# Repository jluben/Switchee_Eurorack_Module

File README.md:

# Switchee Eurorack Module
Switchee is a Eurorack signal switcher using the ATSAMD10D14A. It's a fairly simple design that uses the MCU to control DG447 analog signal switchers. The DG447 a cheap and can handle the full voltage bandwidth of typical Eurorack signals. Assemble is with SMD components, and the PCB falls into budget range of JLCPCB. When this was designed in 2022, you could build a unit for under $30. Even cheaper if you wanted to build ten units.

The default behavior is to advance the output from one to four for each trigger input. The mode button changes this behavior. There are three counting modes: linear, exponential (up to 1024), and fibonacci. In exponential mode, it takes an increase number of triggers to advance the counter and change the output. For example, 2, 4, 8, 16, etc. The fibonacci mode is similiar: it takes 1, 1, 2, 3, 5, 8 and so on triggers to change the output routing.

The module has:
* A TRIGGER input that changes the output
* A Signal input that is buffered and routed to one of four outputs
* A Reset input that changes the switching back to Output One
* A Mode button 

This project includes the PCB, PCB front panel, and firmware. Firmware is downloaded to the ATSAMD10 via ATMEL ICE.

The PCB is done in Kicad. There are fab-ready gerbers in the gerbers/ directory. The main firmware file is in firmware/main.c

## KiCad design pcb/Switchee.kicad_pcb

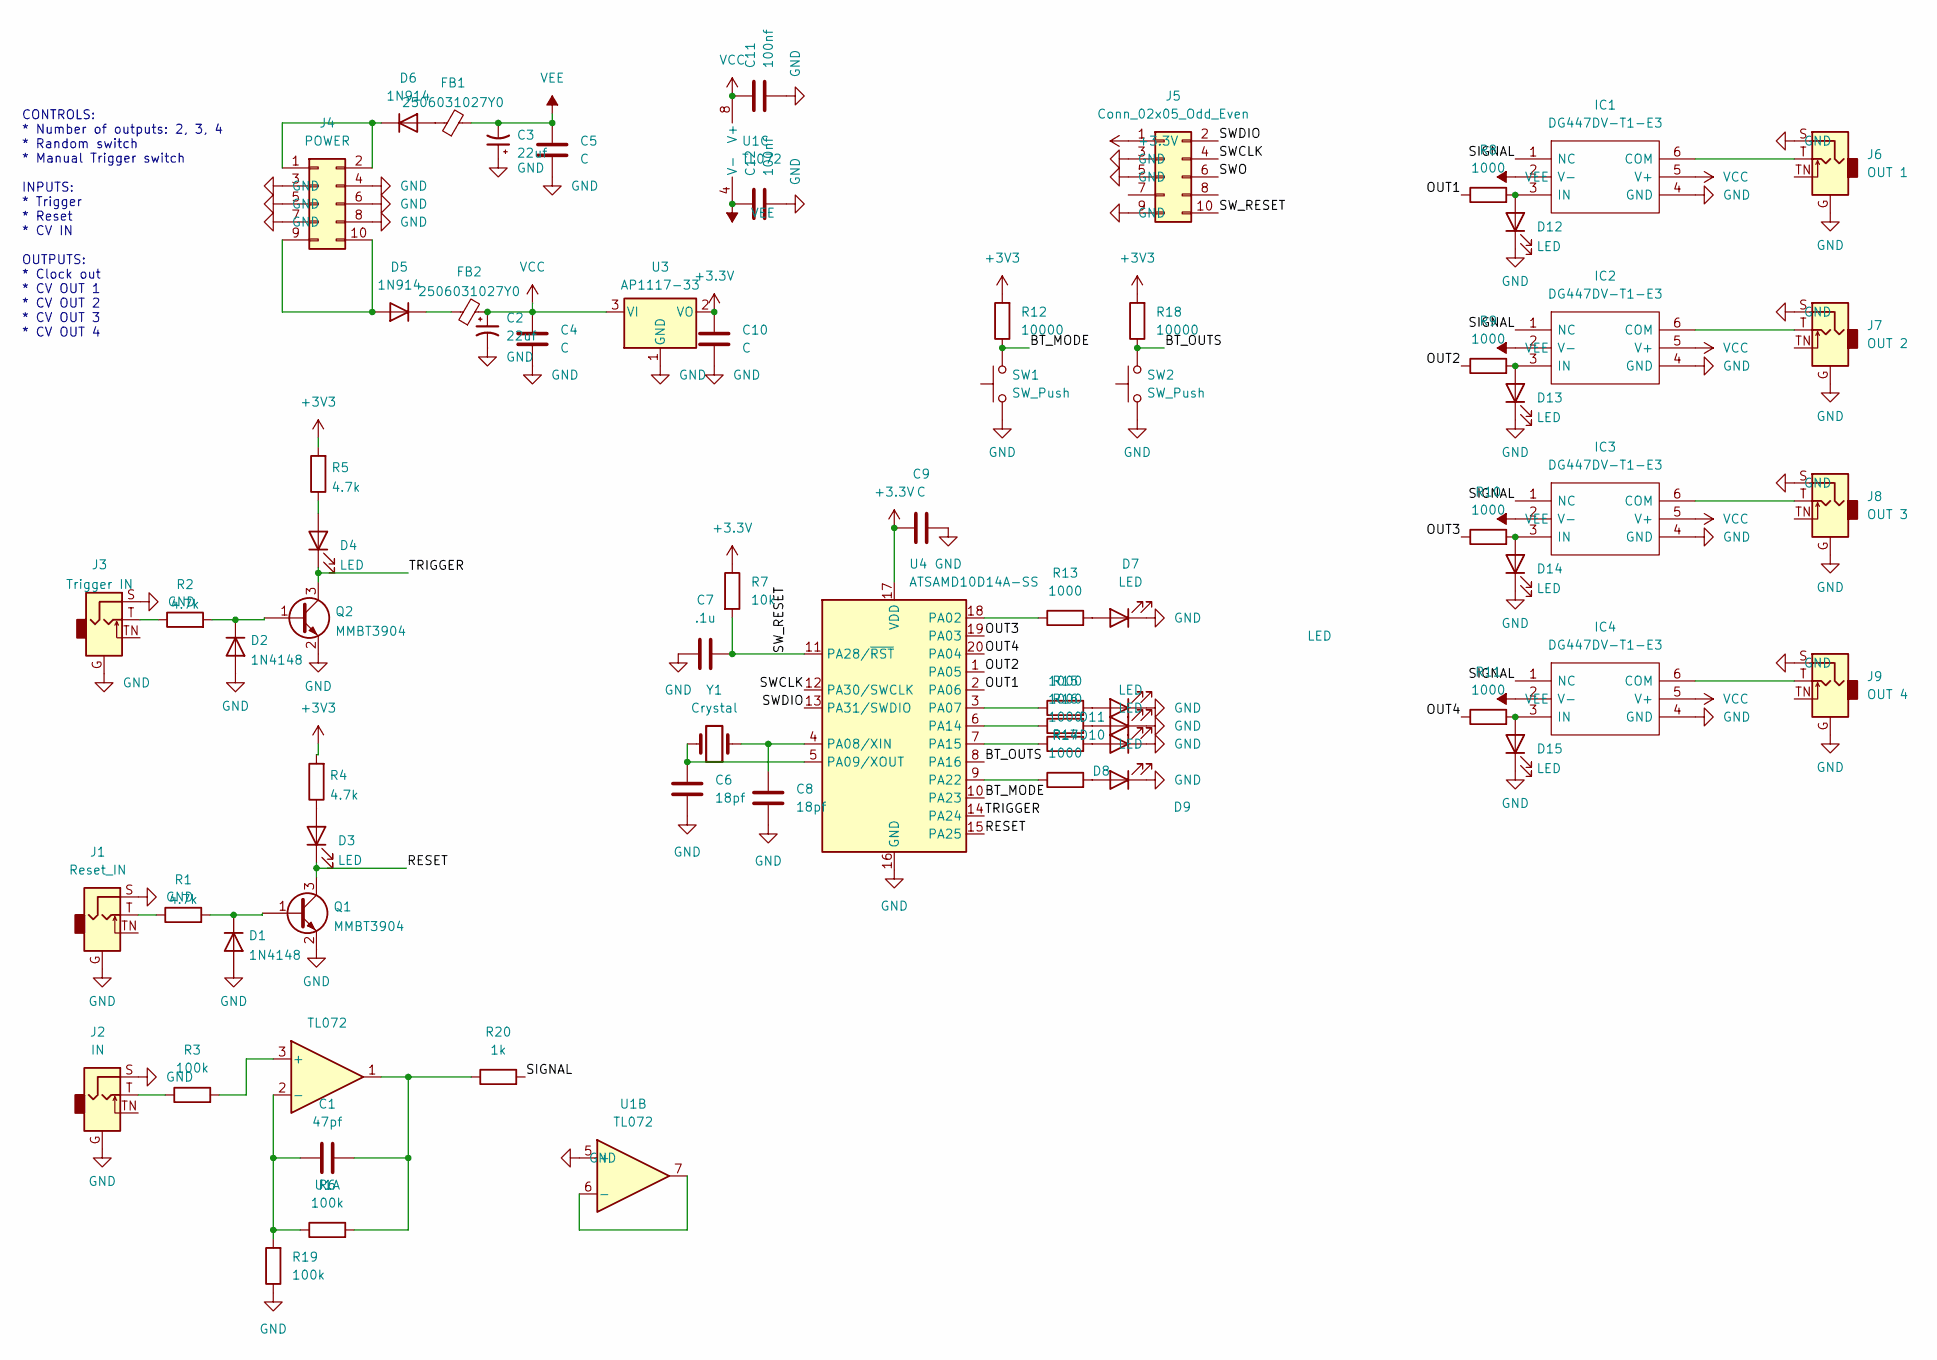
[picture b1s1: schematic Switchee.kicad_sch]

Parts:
C1: 47pf; C_0805_2012Metric_Pad1.18x1.45mm_HandSolder
C2, C3: 22uf; C_1206_3216Metric_Pad1.33x1.80mm_HandSolder
C4, C5, C9, C10: C; C_0805_2012Metric_Pad1.18x1.45mm_HandSolder
C6, C8: 18pf; C_0805_2012Metric_Pad1.18x1.45mm_HandSolder
C7: .1u; C_0805_2012Metric_Pad1.18x1.45mm_HandSolder
C11, C12: 100nf; C_0805_2012Metric_Pad1.18x1.45mm_HandSolder
D1, D2: 1N4148; D_SOD-123
D3, D4, D7, D8, D9, D10, D11, D12, D13, D14, D15: LED; LED_D3.0mm
D5, D6: 1N914; D_SOD-123
FB1, FB2: 2506031027Y0; R_0805_2012Metric_Pad1.20x1.40mm_HandSolder
IC1, IC2, IC3, IC4: DG447DV-T1-E3; SOP95P284X110-6N; Mouser Part Number 781-DG447DV-E3
J1: Reset_IN; Jack_3.5mm_QingPu_WQP-PJ398SM_Vertical_CircularHoles
J2: IN; Jack_3.5mm_QingPu_WQP-PJ398SM_Vertical_CircularHoles
J3: Trigger IN; Jack_3.5mm_QingPu_WQP-PJ398SM_Vertical_CircularHoles
J4: POWER; PinHeader_2x05_P2.54mm_Vertical
J5: Conn_02x05_Odd_Even; PinHeader_2x05_P1.27mm_Vertical
J6: OUT 1; Jack_3.5mm_QingPu_WQP-PJ398SM_Vertical_CircularHoles
J7: OUT 2; Jack_3.5mm_QingPu_WQP-PJ398SM_Vertical_CircularHoles
J8: OUT 3; Jack_3.5mm_QingPu_WQP-PJ398SM_Vertical_CircularHoles
J9: OUT 4; Jack_3.5mm_QingPu_WQP-PJ398SM_Vertical_CircularHoles
Q1, Q2: MMBT3904; SOT-23
R1, R2, R4, R5: 4.7k; R_0805_2012Metric_Pad1.20x1.40mm_HandSolder
R3, R6, R19: 100k; R_0805_2012Metric_Pad1.20x1.40mm_HandSolder
R7: 10k; R_0805_2012Metric_Pad1.20x1.40mm_HandSolder
R8, R9, R10, R11, R13, R14, R15, R16, R17: 1000; R_0805_2012Metric_Pad1.20x1.40mm_HandSolder
R12, R18: 10000; R_0805_2012Metric_Pad1.20x1.40mm_HandSolder
R20: 1k; R_0805_2012Metric_Pad1.20x1.40mm_HandSolder
SW1, SW2: SW_Push; SW_PUSH_6mm
U1: TL072; SOIC-8_3.9x4.9mm_P1.27mm
U3: AP1117-33; SOT-223-3_TabPin2
U4: ATSAMD10D14A-SS; SOIC-20W_7.5x12.8mm_P1.27mm
Y1: Crystal; Crystal_Round_D1.0mm_Vertical

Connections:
/BT_MODE: R12.1, SW1.2, U4.10 (PA23)
/BT_OUTS: R18.1, SW2.2, U4.8 (PA16)
/OUT1: R8.1, U4.2 (PA06)
/OUT2: R9.1, U4.1 (PA05)
/OUT3: R10.1, U4.19 (PA03)
/OUT4: R11.1, U4.20 (PA04)
/RESET: D3.1 (K), Q1.3 (C), U4.15 (PA25)
/SIGNAL: IC1.1 (NC), IC2.1 (NC), IC3.1 (NC), IC4.1 (NC), R20.2
/SWCLK: J5.4, U4.12 (PA30/SWCLK)
/SWDIO: J5.2, U4.13 (PA31/SWDIO)
/SWO: J5.6
/SW_RESET: C7.1, J5.10, R7.2, U4.11 (PA28/~RST)
/TRIGGER: D4.1 (K), Q2.3 (C), U4.14 (PA24)
GND: C2.2, C3.1, C4.2, C5.2, C6.2, C7.2, C8.2, C9.2, C10.2, C11.2, C12.2, D1.2 (A), D2.2 (A), D7.1 (K), D8.1 (K), D9.1 (K), D10.1 (K), D11.1 (K), D12.1 (K), D13.1 (K), D14.1 (K), D15.1 (K), IC1.4 (GND), IC2.4 (GND), IC3.4 (GND), IC4.4 (GND), J1.G, J1.S, J2.G, J2.S, J3.G, J3.S, J4.3, J4.4, J4.5, J4.6, J4.7, J4.8, J5.3, J5.5, J5.9, J6.G, J6.S, J7.G, J7.S, J8.G, J8.S, J9.G, J9.S, Q1.2 (E), Q2.2 (E), R19.1, SW1.1, SW2.1, U1.5 (+), U3.1 (GND), U4.16 (GND)
unnamed: C1.2, R6.2, R20.1, U1.1
unnamed: C6.1, U4.5 (PA09/XOUT), Y1.2
unnamed: C8.1, U4.4 (PA08/XIN), Y1.1
unnamed: D1.1 (K), Q1.1 (B), R1.2
unnamed: D2.1 (K), Q2.1 (B), R2.2
unnamed: D3.2 (A), R4.1
unnamed: D4.2 (A), R5.1
unnamed: D5.1 (K), FB2.1
unnamed: D5.2 (A), J4.9, J4.10
unnamed: D6.1 (K), J4.1, J4.2
unnamed: D6.2 (A), FB1.1
unnamed: D7.2 (A), R13.2
unnamed: D8.2 (A), R14.2
unnamed: D9.2 (A), R15.2
unnamed: D10.2 (A), R16.2
unnamed: D11.2 (A), R17.2
unnamed: D12.2 (A), IC1.3 (IN), R8.2
unnamed: D13.2 (A), IC2.3 (IN), R9.2
unnamed: D14.2 (A), IC3.3 (IN), R10.2
unnamed: D15.2 (A), IC4.3 (IN), R11.2
unnamed: IC1.6 (COM), J6.T
unnamed: IC2.6 (COM), J7.T
unnamed: IC3.6 (COM), J8.T
unnamed: IC4.6 (COM), J9.T
unnamed: J1.T, R1.1
unnamed: J2.T, R3.1
unnamed: J3.T, R2.1
unnamed: R3.2, U1.3 (+)
unnamed: R13.1, U4.18 (PA02)
unnamed: R14.1, U4.9 (PA22)
unnamed: R15.1, U4.6 (PA14)
unnamed: R16.1, U4.7 (PA15)
unnamed: R17.1, U4.3 (PA07)
unnamed: C1.1, R6.1, R19.2, U1.2 (-)
unnamed: U1.6 (-), U1.7
VCC: C2.1, C4.1, C11.1, FB2.2, IC1.5 (V+), IC2.5 (V+), IC3.5 (V+), IC4.5 (V+), U1.8 (V+), U3.3 (VI)
VEE: C3.2, C5.1, C12.1, FB1.2, IC1.2 (V-), IC2.2 (V-), IC3.2 (V-), IC4.2 (V-), U1.4 (V-)

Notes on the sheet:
CONTROLS: * Number of outputs: 2, 3, 4 * Random switch * Manual Trigger switch INPUTS: * Trigger * Reset * CV IN OUTPUTS: * Clock out * CV OUT 1 * CV OUT 2 * CV OUT 3 * CV OUT 4

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
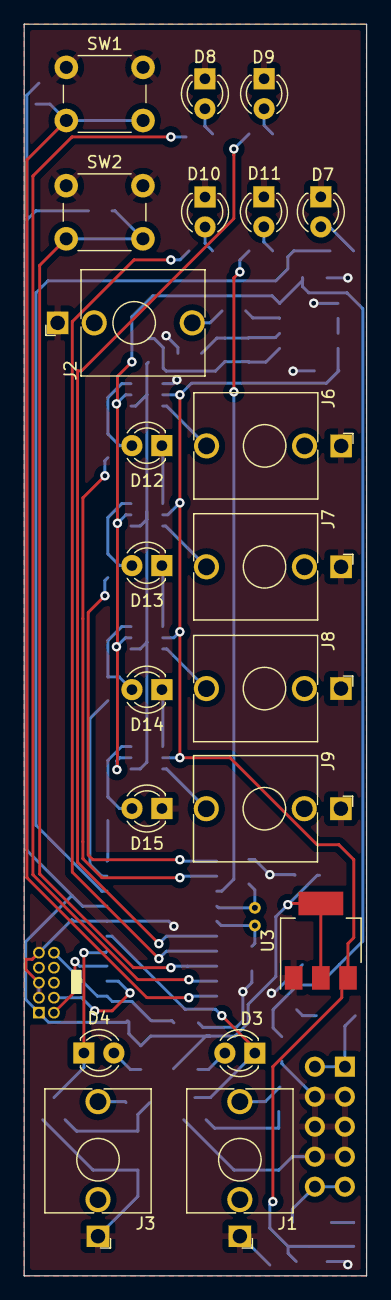
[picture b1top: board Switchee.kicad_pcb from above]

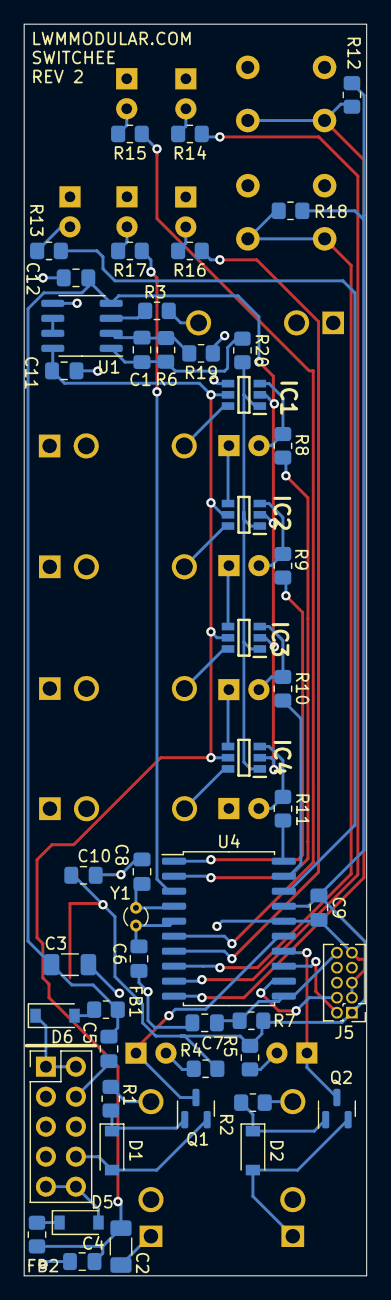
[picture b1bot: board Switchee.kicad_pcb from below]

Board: 2 copper layers, 29.0 x 106.0 mm, 70 parts (49 on the bottom side), 51 nets.

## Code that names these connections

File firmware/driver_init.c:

/*
 * Code generated from Atmel Start.
 *
 * This file will be overwritten when reconfiguring your Atmel Start project.
 * Please copy examples or other code you want to keep to a separate file
 * to avoid losing it when reconfiguring.
 */

#include "driver_init.h"
#include <peripheral_clk_config.h>
#include <utils.h>
#include <hal_init.h>
#include <hpl_gclk_base.h>
#include <hpl_pm_base.h>

#include <hpl_rtc_base.h>

struct timer_descriptor TIMER_0;

struct flash_descriptor FLASH_0;

struct dac_sync_descriptor DAC_0;

void FLASH_0_CLOCK_init(void)
{

	_pm_enable_bus_clock(PM_BUS_APBB, NVMCTRL);
}

void FLASH_0_init(void)
{
	FLASH_0_CLOCK_init();
	flash_init(&FLASH_0, NVMCTRL);
}

void delay_driver_init(void)
{
	delay_init(SysTick);
}

/**
 * \brief Timer initialization function
 *
 * Enables Timer peripheral, clocks and initializes Timer driver
 */
static void TIMER_0_init(void)
{
	_pm_enable_bus_clock(PM_BUS_APBA, RTC);
	_gclk_enable_channel(RTC_GCLK_ID, CONF_GCLK_RTC_SRC);
	timer_init(&TIMER_0, RTC, _rtc_get_timer());
}

void DAC_0_PORT_init(void)
{
}

void DAC_0_CLOCK_init(void)
{

	_pm_enable_bus_clock(PM_BUS_APBC, DAC);
	_gclk_enable_channel(DAC_GCLK_ID, CONF_GCLK_DAC_SRC);
}

void DAC_0_init(void)
{
	DAC_0_CLOCK_init();
	dac_sync_init(&DAC_0, DAC);
	DAC_0_PORT_init();
}

void system_init(void)
{
	init_mcu();

	// GPIO on PA02

	// Disable digital pin circuitry
	gpio_set_pin_direction(LED7, GPIO_DIRECTION_OFF);

	gpio_set_pin_function(LED7, GPIO_PIN_FUNCTION_OFF);

	// GPIO on PA03

	gpio_set_pin_level(OUT3,
	                   // <y> Initial level
	                   // <id> pad_initial_level
	                   // <false"> Low
	                   // <true"> High
	                   false);

	// Set pin direction to output
	gpio_set_pin_direction(OUT3, GPIO_DIRECTION_OUT);

	gpio_set_pin_function(OUT3, GPIO_PIN_FUNCTION_OFF);

	// GPIO on PA04

	gpio_set_pin_level(OUT4,
	                   // <y> Initial level
	                   // <id> pad_initial_level
	                   // <false"> Low
	                   // <true"> High
	                   false);

	// Set pin direction to output
	gpio_set_pin_direction(OUT4, GPIO_DIRECTION_OUT);

	gpio_set_pin_function(OUT4, GPIO_PIN_FUNCTION_OFF);

	// GPIO on PA05

	gpio_set_pin_level(OUT2,
	                   // <y> Initial level
	                   // <id> pad_initial_level
	                   // <false"> Low
	                   // <true"> High
	                   false);

	// Set pin direction to output
	gpio_set_pin_direction(OUT2, GPIO_DIRECTION_OUT);

	gpio_set_pin_function(OUT2, GPIO_PIN_FUNCTION_OFF);

	// GPIO on PA06

	gpio_set_pin_level(OUT1,
	                   // <y> Initial level
	                   // <id> pad_initial_level
	                   // <false"> Low
	                   // <true"> High
	                   false);

	// Set pin direction to output
	gpio_set_pin_direction(OUT1, GPIO_DIRECTION_OUT);

	gpio_set_pin_function(OUT1, GPIO_PIN_FUNCTION_OFF);

	// GPIO on PA07

	gpio_set_pin_level(LED11,
	                   // <y> Initial level
	                   // <id> pad_initial_level
	                   // <false"> Low
	                   // <true"> High
	                   false);

	// Set pin direction to output
	gpio_set_pin_direction(LED11, GPIO_DIRECTION_OUT);

	gpio_set_pin_function(LED11, GPIO_PIN_FUNCTION_OFF);

	// GPIO on PA14

	gpio_set_pin_level(LED9,
	                   // <y> Initial level
	                   // <id> pad_initial_level
	                   // <false"> Low
	                   // <true"> High
	                   false);

	// Set pin direction to output
	gpio_set_pin_direction(LED9, GPIO_DIRECTION_OUT);

	gpio_set_pin_function(LED9, GPIO_PIN_FUNCTION_OFF);

	// GPIO on PA15

	gpio_set_pin_level(LED10,
	                   // <y> Initial level
	                   // <id> pad_initial_level
	                   // <false"> Low
	                   // <true"> High
	                   false);

	// Set pin direction to output
	gpio_set_pin_direction(LED10, GPIO_DIRECTION_OUT);

	gpio_set_pin_function(LED10, GPIO_PIN_FUNCTION_OFF);

	// GPIO on PA16

	// Set pin direction to input
	gpio_set_pin_direction(SW_OUT, GPIO_DIRECTION_IN);

	gpio_set_pin_pull_mode(SW_OUT,
	                       // <y> Pull configuration
	                       // <id> pad_pull_config
	                       // <GPIO_PULL_OFF"> Off
	                       // <GPIO_PULL_UP"> Pull-up
	                       // <GPIO_PULL_DOWN"> Pull-down
	                       GPIO_PULL_OFF);

	gpio_set_pin_function(SW_OUT, GPIO_PIN_FUNCTION_OFF);

	// GPIO on PA22

	gpio_set_pin_level(LED8,
	                   // <y> Initial level
	                   // <id> pad_initial_level
	                   // <false"> Low
	                   // <true"> High
	                   false);

	// Set pin direction to output
	gpio_set_pin_direction(LED8, GPIO_DIRECTION_OUT);

	gpio_set_pin_function(LED8, GPIO_PIN_FUNCTION_OFF);

	// GPIO on PA23

	// Set pin direction to input
	gpio_set_pin_direction(SW_MODE, GPIO_DIRECTION_IN);

	gpio_set_pin_pull_mode(SW_MODE,
	                       // <y> Pull configuration
	                       // <id> pad_pull_config
	                       // <GPIO_PULL_OFF"> Off
	                       // <GPIO_PULL_UP"> Pull-up
	                       // <GPIO_PULL_DOWN"> Pull-down
	                       GPIO_PULL_OFF);

	gpio_set_pin_function(SW_MODE, GPIO_PIN_FUNCTION_OFF);

	// GPIO on PA24

	// Set pin direction to input
	gpio_set_pin_direction(IN_TRIGGER, GPIO_DIRECTION_IN);

	gpio_set_pin_pull_mode(IN_TRIGGER,
	                       // <y> Pull configuration
	                       // <id> pad_pull_config
	                       // <GPIO_PULL_OFF"> Off
	                       // <GPIO_PULL_UP"> Pull-up
	                       // <GPIO_PULL_DOWN"> Pull-down
	                       GPIO_PULL_OFF);

	gpio_set_pin_function(IN_TRIGGER, GPIO_PIN_FUNCTION_OFF);

	// GPIO on PA25

	// Set pin direction to input
	gpio_set_pin_direction(IN_RESET, GPIO_DIRECTION_IN);

	gpio_set_pin_pull_mode(IN_RESET,
	                       // <y> Pull configuration
	                       // <id> pad_pull_config
	                       // <GPIO_PULL_OFF"> Off
	                       // <GPIO_PULL_UP"> Pull-up
	                       // <GPIO_PULL_DOWN"> Pull-down
	                       GPIO_PULL_OFF);

	gpio_set_pin_function(IN_RESET, GPIO_PIN_FUNCTION_OFF);

	FLASH_0_init();

	delay_driver_init();

	TIMER_0_init();

	DAC_0_init();
}

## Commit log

2024-02-28 initial checkin; moving from BitBucket
2024-02-28 Refine the readme
2024-02-28 Add top of file comments
2024-02-28 Add more preview images
